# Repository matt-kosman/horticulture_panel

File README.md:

# horticulture_panel
Inspired by a recent Great Scott [video](https://www.youtube.com/watch?v=4FryMPpJG6I) and a coincidental attempt to kickstart my balcony garden for the upcoming season, I attempted a reimplementation of the Würth Elektronik [Lighting Development Kit's](https://www.we-online.com/catalog/en/LIGHTING_DEVELOPMENT_KIT) horticulture panel.

<p align="center"></br><b>completed panel illuminating my kitchen garden</b></p>

This design maintains the same wavelengths and corresponding maximum power outputs as the reference design while merging all of the LEDs, drivers, and simplified manual dimming controls onto a single compact PCB.

<p align="center"></br><b>panel assembly with candidate heatsink</b></p>

The files needed to build a panel for yourself are located in the [build](/build) directory, and the KiCAD source files, libraries, and models in the [kicad](/kicad) directory. I recommend reading this description before proceeding, as there are important considerations throughout - particularly about PCB assembly and thermal management.

# design

## LED and drivers
This design uses the same type and quantity of LEDs as the Würth Elektronik panel. There are four different types of LEDs, targeting the wavelengths needed to promote various stages of plant growth. LEDs of the same wavelength are connected in series to a single constant current LED driver, so they can be dimmed together. Both fixed 350mA and adjustable resistor footprints are available, but only one should be populated at a time.

<p align="center"></br><b>two of the six <i>hyper red</i> LEDs and their associated driver</b></p>

The LEDs are arranged in a grid with 12.5mm spacing to fit the selected Ledil C16597 lens. The footprints for the LEDs and drivers were expanded to allow hand soldering.

<p align="center"></br><b>LED array with expanded footprints and lens mounting holes</b></p>

## thermal

Heat is a key consideration. A simple estimate - considering the total power delivered minus the power emitted as light - suggests an approximate output power of 6W of light and 8W of heat.

| LED Type  | Forward Voltage @ 350mA | Power In | Radiant Flux | Heat   | Quantity |
|:----------|:------------------------|:---------|:-------------|:-------|:---------|
| Hyper Red | 2.2 V                   | 0.77 W   | 0.44 W       | 0.33 W | 6        |
| Deep Blue | 3.2 V                   | 1.12 W   | 0.60 W       | 0.52 W | 2        |
| Far Red   | 1.8 V                   | 0.63 W   | 0.35 W       | 0.28 W | 4        |
| Daylight  | 3.2 V                   | 1.12 W   | 0.20 W est.  | 0.92 W | 4        |

This is the extent of the formal thermal analysis. However, heat dissipation was a key part of the PCB design. Vias were placed underneath the LED and driver thermal pads, in addition to a grid of vias in the area near the LEDs and drivers. The rear side of the PCB has no components and is almost entirely ground plane. This both promotes heat transfer to the heat sink and minimizes the risk of shorts to ground. The four traces that do traverse the bottom side contain the low-energy PWM signals. There are a number of mounting holes near the LEDs and drivers to attach a heatsink.

<p align="center"></br><b>PCB rear showing ground plane, thermal vias, mounting holes, and PWM trace traversal</b></p>

My candidate heatsink is a section of McMaster [6546K2](https://www.mcmaster.com/6546K2/) 2x1-inch rectangular aluminum extrusion, cut to length, drilled, and tapped. A layer of kapton tape between the heatink and PCB provides an additional layer of isolation from the PWM traces and acts as a basic thermal pad. Specific results will depend on your heatsink and thermal environment. The included step file can assist with locating mounting holes and designing the mechanical interface.

## control
While the LED drivers have an adjustable current output, PWM control preserves the color characteristics of the LEDs - which are nominally designed for 350mA - and allows dimming to zero intensity.

This design uses four Analog Devices LTC6992-1 voltage-controlled pulse width modulators to convert analog outputs from four corresponding potentiometers into the required control signals. A convenient [online tool](http://beta-tools.analog.com/timerblox/LTC6992) simplifies the design of LTC6992 circuits. The selected resistors produce an operating frequency of approximately 220Hz, which should exceed the [flicker fusion threshold](https://en.wikipedia.org/wiki/Flicker_fusion_threshold) in most cases and approximates the 244Hz example in the LED driver datasheet.

Despite the possible reductions in size and cost, I decided not to use a microcontroller for PWM control. Primarily, I wanted to avoid software as part of this project. However, the apparent benefits of a microcontroller are also somewhat offset by the I/O requirements (minimum 4 analog input and 4 PWM output), additional power draw on the 5V supply, and need for programming headers.

<p align="center"></br><b>control circuit</b></p>

Sourcing a suitable surface mount potentiometer was surprisingly difficult. The resulting linear potentiometer provides clear visual feedback when the panel is unpowered. There are four copies of the same circuit, aligned for easy hand soldering, with compromises as required to the recommended layout.

<p align="center"></br><b>layout of qty(4) control circuits</b></p>

Absent a control input, LED drivers will operate at 100% duty cycle. Depending on your application and desire to adjust light intensities, you may choose to omit the control elements for one or more of the drivers.

## power
The six series Hyper Red LEDs may need up to 15.6V to overcome the worst-case forward drop of 2.6V (vs. 2.2V typical). The panel accepts a nominal 20V through a 2.5x5.5mm barrel jack, with center positive and barrel ground. I use a USB Power Delivery mains adapter with 20V trigger cable. There is a 2A fuse at the input sized to protect the smallest 20V trace. The input power is not reverse polarity protected or filtered.

The control circuits require 5V power, which is provided by a linear regulator. The control circuit current is on the order of 1mA - well below the capability of the selected ZXTR2105F regulator with 20V input.

<p align="center"></br><b>power input and 5V regulator</b></p>

# assembly

This is a challenging assembly, but it is designed for hand soldering with the right equipment. The primary challenges are the large ground planes needed for heat dissipation during operation, and the relatively small footprints.

<p align="center"></br><b>bare PCB with candidate heatsink stock</b></p>

I achieved a successful result soldering the LEDs using a [Miniware MHP30](http://www.miniware.com.cn/product/mhp30-mini-hot-plate-preheater/) to locally preheat to 150°C, manually applying solder paste, then soldering each joint for 15 seconds at 300°C with an iron.

The thermal pad of the LED drivers does not extend to the edge of the package like a typical TO263-7. While I designed enough extra pad area to hand solder the thermal pad using a similar process to the LEDs, I decided to reflow with the hot plate and also achieved a successful result.

<p align="center"></br><b>populated PCB</b></p>

The remaining components are standard surface mount and can be soldered according to your preferred technique.

# performance

Qualitatively, the lights turn on, are very bright, and change intensity as expected.

The linear potentiometers are usable, if compact, and provide passive visual feedback about their positions even with the light off. While the Bluetooth and app-based control of the Würth Elektronik kit is perhaps better suited to demonstrate the extent of possible horticultural applications, I find the manual interface to be more direct and useful for my occasional adjustments.

My USB PD wattmeter shows 17W, which aligns reasonably well with the 14W predicted and is easily explained by higher than typical forward voltages in some of the LEDs.

<p align="center"></br><b>thermal checkout showing steady state temperature with all lights at 100%</b></p>

The heatsink is capable of maintaining 80°C steady state in a 20°C room without airflow and with all lights at 100% power. In practice, to achieve the correct mix of wavelengths for each growth phase, not all of the lights will be active or at 100%; so the practical working temperatures will be lower. For comparison, the LED bulbs I use for home lighting consume 6W and reach a temperature of 65°C, which suggests this is a reasonable result. Your requirements will vary and will inform the design of your heatsink and mounting solutions.

Regarding plant growth, it's too soon to tell.

# revision history
## Rev. A 2022-03-05
### changelog
Initial release.

### known issues
1. When a LED channel is commanded to 0% duty cycle, touching that channel's driver circuit can command the lights to flicker. I believe this is caused by the relatively high 50kΩ resistance of the potentiometer circuit failing to overcome the stray voltages and can be solved by selecting a lower value potentiometer - taking note of total current from the 5V regualtor - or adding a buffer stage near the potentiometer before wiring to the PWM converter.

1. The selected 10kΩ potentiometer is paired with a 39kΩ series resistor to provide 0V to 1.02V to the LTC6992 converter. This range is slightly biased towards allowing 100% brightness and does not account for the tolerances of the selected parts. In practice,  human precision and the short travel of the linear potentiometers are the limiting factors in selecting the brightness level, but the circuit could be tuned if desired by including a trimmer to adjust the upper limit closer to 1V.

1. While the sequential arrangement of LEDs simplifies trace routing and allows all power traces to be on the top layer, it also clusters LEDs of the same wavelength together and might cause certain plants to receive more of one type of light than another. For my intended home use, I will solve this by maintaining a reasonable distance between the panel and plants, but a larger array might consider a different arrangement.

# license
 The horticulture_panel is licensed under [CC BY-NC-SA 4.0](https://creativecommons.org/licenses/by-nc-sa/4.0/). Attribution may be provided by link to this repository.

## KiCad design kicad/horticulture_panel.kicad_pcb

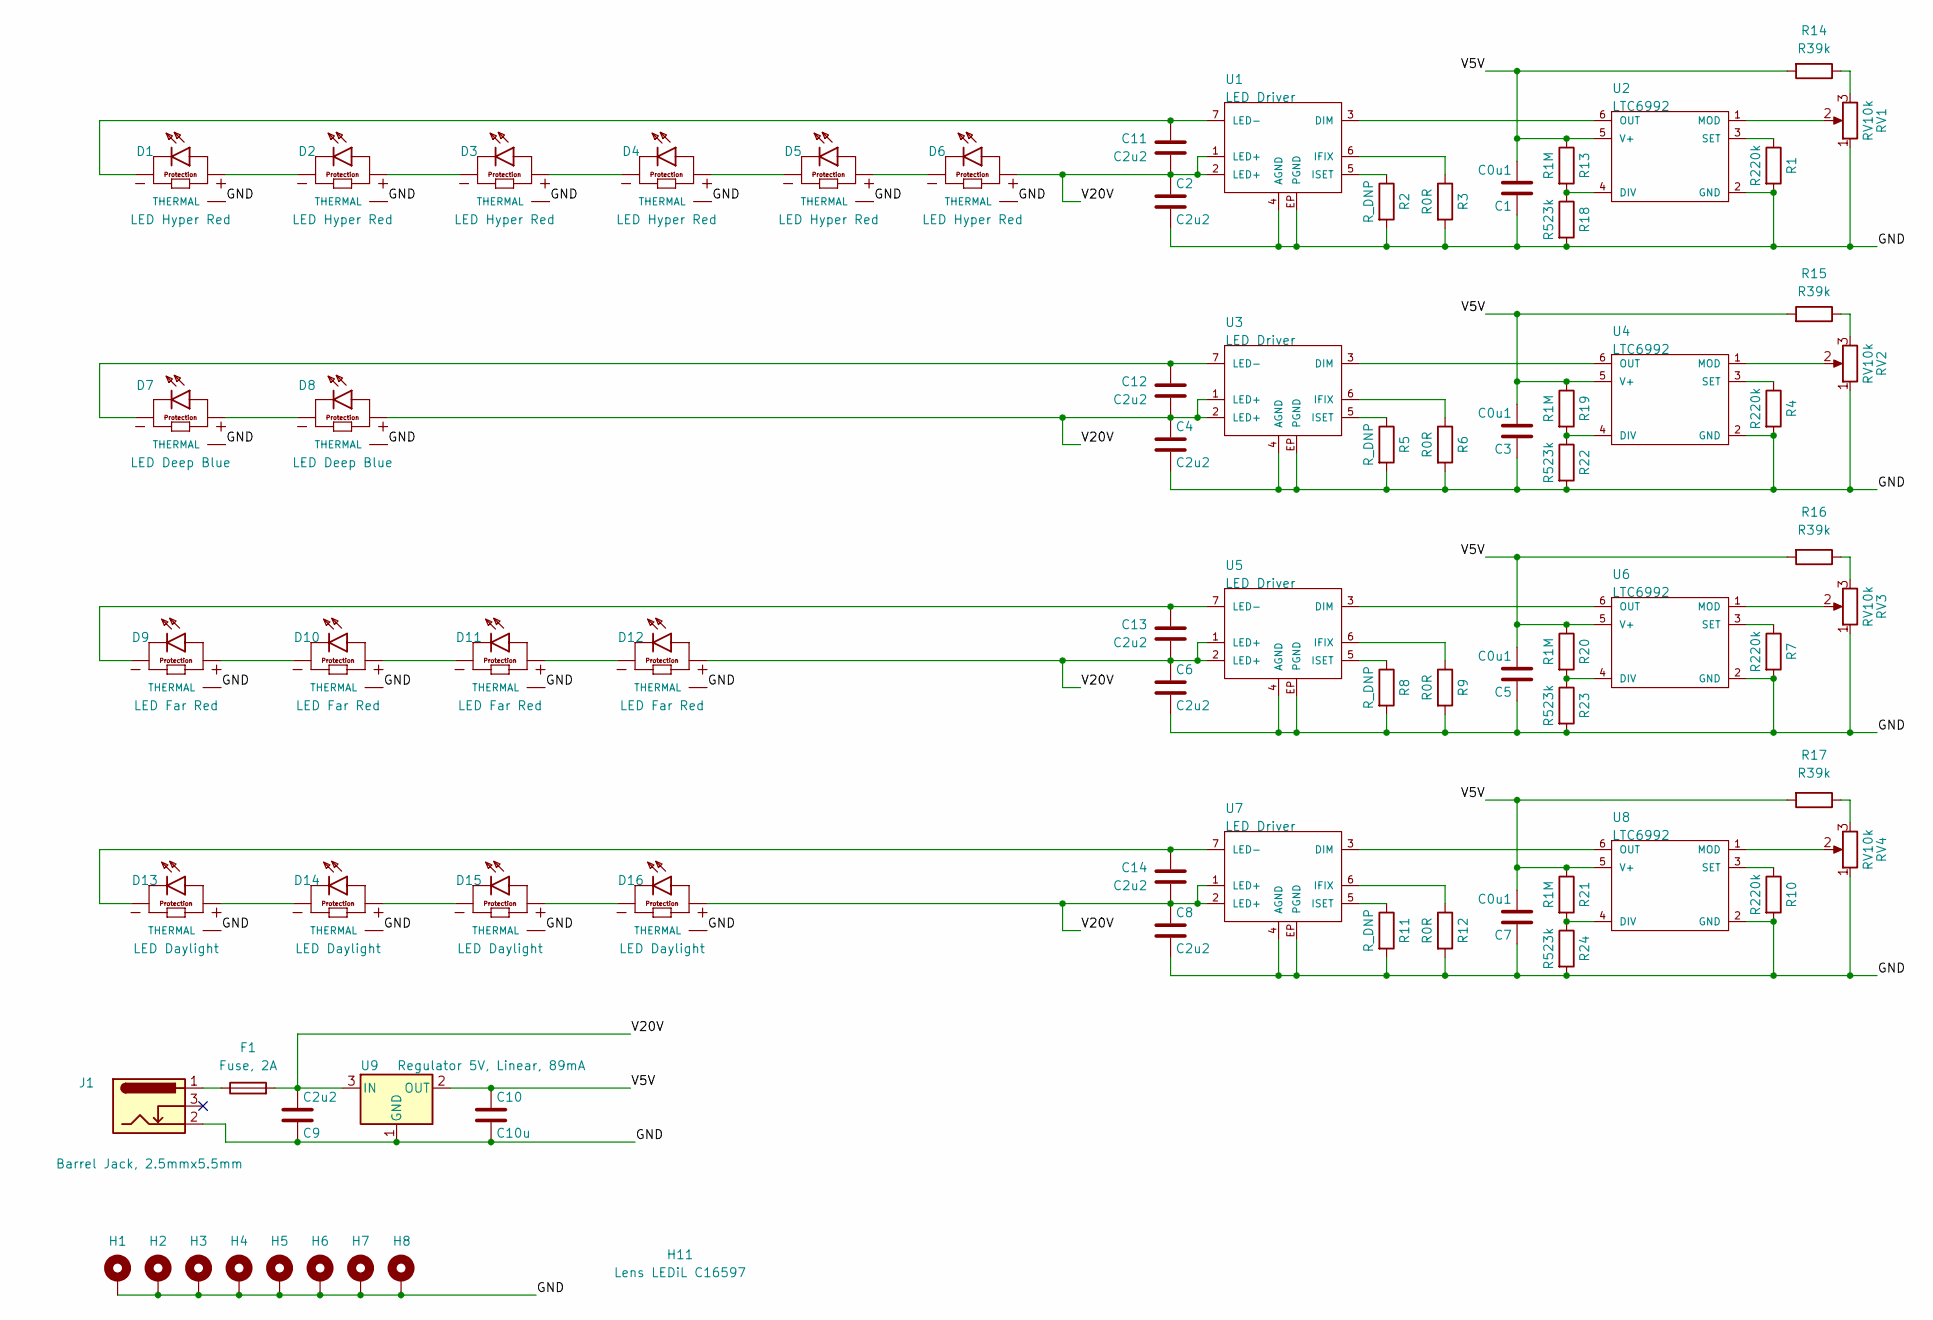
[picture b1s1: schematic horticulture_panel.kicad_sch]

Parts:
C1, C3, C5, C7: C0u1; C0805; MPN CL21B104KBCNNNC
C2, C4, C6, C8, C9, C11, C12, C13, C14: C2u2; C1210; MPN CL32B225KCJSNNE
C10: C10u; C0805; MPN CL21B106KPQNNNE
D1, D2, D3, D4, D5, D6: LED Hyper Red; Wurth Elektronik 3535 LED; MPN 150353HS74500
D7, D8: LED Deep Blue; Wurth Elektronik 3535 LED; MPN 150353DS74500
D9, D10, D11, D12: LED Far Red; Wurth Elektronik 3535 LED; MPN 150353FS74500
D13, D14, D15, D16: LED Daylight; Wurth Elektronik 3535 LED; MPN 158353050
F1: Fuse, 2A; Littelfuse 154; MPN 0154002.DR
H1, H2, H3, H4, H5, H6, H7, H8: Mounting Hole; Mounting Hole #4
H11: Lens LEDiL C16597; LEDiL C16597; MPN C16597
J1: Barrel Jack, 2.5mmx5.5mm; CUI PJ-036BH; MPN PJ-036BH-SMT-TR
R1, R4, R7, R10: R220k; R0805; MPN RMCF0805JT220K
R2, R5, R8, R11: R_DNP; DNP_0805
R3, R6, R9, R12: R0R; R0805; MPN RMCF0805ZT0R00
R13, R19, R20, R21: R1M; R0805; MPN RMCF0805JT1M00
R14, R15, R16, R17: R39k; R0805; MPN RMCF0805JT39K0
R18, R22, R23, R24: R523k; R0805; MPN RMCF0805FT523K
RV1, RV2, RV3, RV4: RV10k; PSM050S-10; MPN PSM050S-10B10KB
U1, U3, U5, U7: LED Driver; Wurth Elektronik LED Driver TO-263-7; MPN 172946001
U2, U4, U6, U8: LTC6992; SOT-23-6; MPN LTC6992
U9: Regulator 5V, Linear, 89mA; SOT-23; MPN ZXTR2105F-7

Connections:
/GND: C1.1, C2.2, C3.1, C4.2, C5.1, C6.2, C7.1, C8.2, C9.1, C10.2, D1.3 (THERMAL), D2.3 (THERMAL), D3.3 (THERMAL), D4.3 (THERMAL), D5.3 (THERMAL), D6.3 (THERMAL), D7.3 (THERMAL), D8.3 (THERMAL), D9.3 (THERMAL), D10.3 (THERMAL), D11.3 (THERMAL), D12.3 (THERMAL), D13.3 (THERMAL), D14.3 (THERMAL), D15.3 (THERMAL), D16.3 (THERMAL), H1.1, H2.1, H3.1, H4.1, H5.1, H6.1, H7.1, H8.1, J1.2, R1.2, R2.2, R3.2, R4.2, R5.2, R6.2, R7.2, R8.2, R9.2, R10.2, R11.2, R12.2, R18.2, R22.2, R23.2, R24.2, RV1.1, RV2.1, RV3.1, RV4.1, U1.4 (AGND), U1.EP (PGND), U2.2 (GND), U3.4 (AGND), U3.EP (PGND), U4.2 (GND), U5.4 (AGND), U5.EP (PGND), U6.2 (GND), U7.4 (AGND), U7.EP (PGND), U8.2 (GND), U9.1 (GND)
/V5V: C1.2, C3.2, C5.2, C7.2, C10.1, R13.1, R14.2, R15.2, R16.2, R17.2, R19.1, R20.1, R21.1, U2.5 (V+), U4.5 (V+), U6.5 (V+), U8.5 (V+), U9.2 (OUT)
/V20V: C2.1, C4.1, C6.1, C8.1, C9.2, C11.1, C12.1, C13.1, C14.1, D6.2, D8.2, D12.2, D16.2, F1.2, U1.1 (LED+), U1.2 (LED+), U3.1 (LED+), U3.2 (LED+), U5.1 (LED+), U5.2 (LED+), U7.1 (LED+), U7.2 (LED+), U9.3 (IN)
unnamed: C11.2, D1.1, U1.7 (LED-)
unnamed: C12.2, D7.1, U3.7 (LED-)
unnamed: C13.2, D9.1, U5.7 (LED-)
unnamed: C14.2, D13.1, U7.7 (LED-)
unnamed: D1.2, D2.1
unnamed: D2.2, D3.1
unnamed: D3.2, D4.1
unnamed: D4.2, D5.1
unnamed: D5.2, D6.1
unnamed: D7.2, D8.1
unnamed: D9.2, D10.1
unnamed: D10.2, D11.1
unnamed: D11.2, D12.1
unnamed: D13.2, D14.1
unnamed: D14.2, D15.1
unnamed: D15.2, D16.1
unnamed: F1.1, J1.1
unnamed: R1.1, U2.3 (SET)
unnamed: R2.1, U1.5 (ISET)
unnamed: R3.1, U1.6 (IFIX)
unnamed: R4.1, U4.3 (SET)
unnamed: R5.1, U3.5 (ISET)
unnamed: R6.1, U3.6 (IFIX)
unnamed: R7.1, U6.3 (SET)
unnamed: R8.1, U5.5 (ISET)
unnamed: R9.1, U5.6 (IFIX)
unnamed: R10.1, U8.3 (SET)
unnamed: R11.1, U7.5 (ISET)
unnamed: R12.1, U7.6 (IFIX)
unnamed: R13.2, R18.1, U2.4 (DIV)
unnamed: R14.1, RV1.3
unnamed: R15.1, RV2.3
unnamed: R16.1, RV3.3
unnamed: R17.1, RV4.3
unnamed: R19.2, R22.1, U4.4 (DIV)
unnamed: R20.2, R23.1, U6.4 (DIV)
unnamed: R21.2, R24.1, U8.4 (DIV)
unnamed: RV1.2, U2.1 (MOD)
unnamed: RV2.2, U4.1 (MOD)
unnamed: RV3.2, U6.1 (MOD)
unnamed: RV4.2, U8.1 (MOD)
unnamed: U1.3 (DIM), U2.6 (OUT)
unnamed: U3.3 (DIM), U4.6 (OUT)
unnamed: U5.3 (DIM), U6.6 (OUT)
unnamed: U7.3 (DIM), U8.6 (OUT)

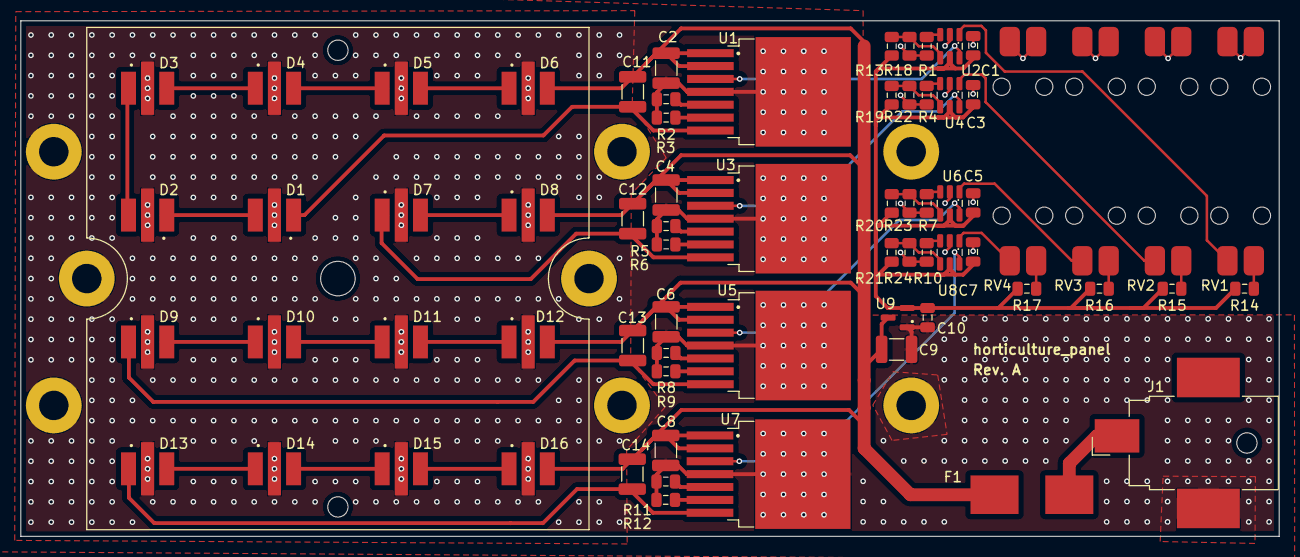
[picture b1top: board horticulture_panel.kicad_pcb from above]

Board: 2 copper layers, 124.0 x 50.8 mm, 78 parts (0 on the bottom side), 48 nets.

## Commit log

2022-03-29 add rev A project files
2022-03-29 add readme and license
